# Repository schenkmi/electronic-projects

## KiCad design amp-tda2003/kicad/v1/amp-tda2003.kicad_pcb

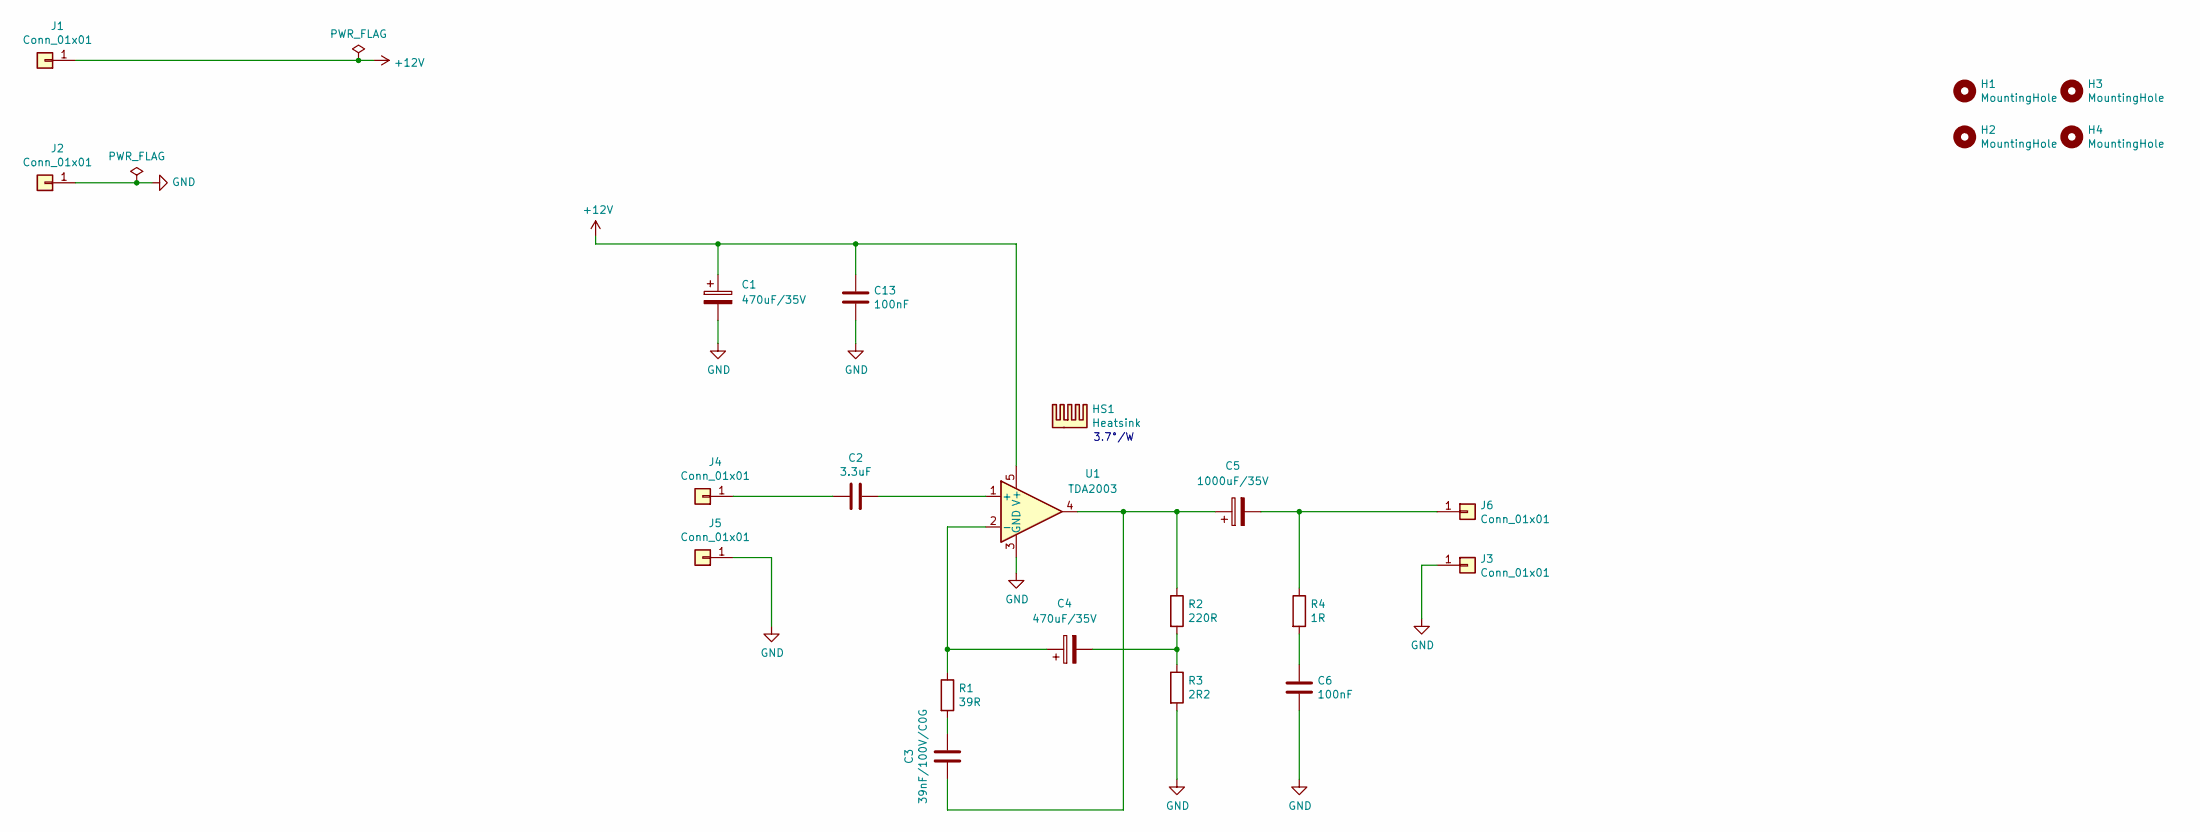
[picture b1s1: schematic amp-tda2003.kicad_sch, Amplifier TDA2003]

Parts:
C1, C4: 470uF/35V; CP_Radial_D10.0mm_P5.00mm
C2: 3.3uF; C_Rect_L7.2mm_W7.2mm_P5.00mm_FKS2_FKP2_MKS2_MKP2
C3: 39nF/100V/C0G; C_0805_2012Metric_Pad1.18x1.45mm_HandSolder
C5: 1000uF/35V; CP_Radial_D12.5mm_P5.00mm
C6, C13: 100nF; C_1206_3216Metric_Pad1.33x1.80mm_HandSolder
H1, H2, H3, H4: MountingHole; MountingHole_3.2mm_M3_Pad_Via
HS1: Heatsink; Heatsink_Fischer_SK129-STS_42x25mm_2xDrill2.5mm
J1, J2, J3, J4, J5, J6: Conn_01x01; Pin_D1.0mm_L10.0mm
R1: 39R; R_0805_2012Metric_Pad1.20x1.40mm_HandSolder
R2: 220R; R_0805_2012Metric_Pad1.20x1.40mm_HandSolder
R3: 2R2; R_0805_2012Metric_Pad1.20x1.40mm_HandSolder
R4: 1R; R_0805_2012Metric_Pad1.20x1.40mm_HandSolder
U1: TDA2003; TO-220-5_P3.4x3.7mm_StaggerOdd_Lead3.8mm_Vertical

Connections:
+12V: C1.1, C13.2, J1.1, U1.5 (V+)
GND: C1.2, C6.1, C13.1, J2.1, J3.1, J5.1, R3.2, U1.3 (GND)
unnamed: C3.1, R1.2
unnamed: C3.2, C5.1, R2.1, U1.4
unnamed: C4.2, R2.2, R3.1
unnamed: C6.2, R4.2
unnamed: C2.2, J4.1
unnamed: C5.2, J6.1, R4.1
unnamed: C2.1, U1.1 (+)
unnamed: C4.1, R1.1, U1.2 (-)

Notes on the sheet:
3.7°/W

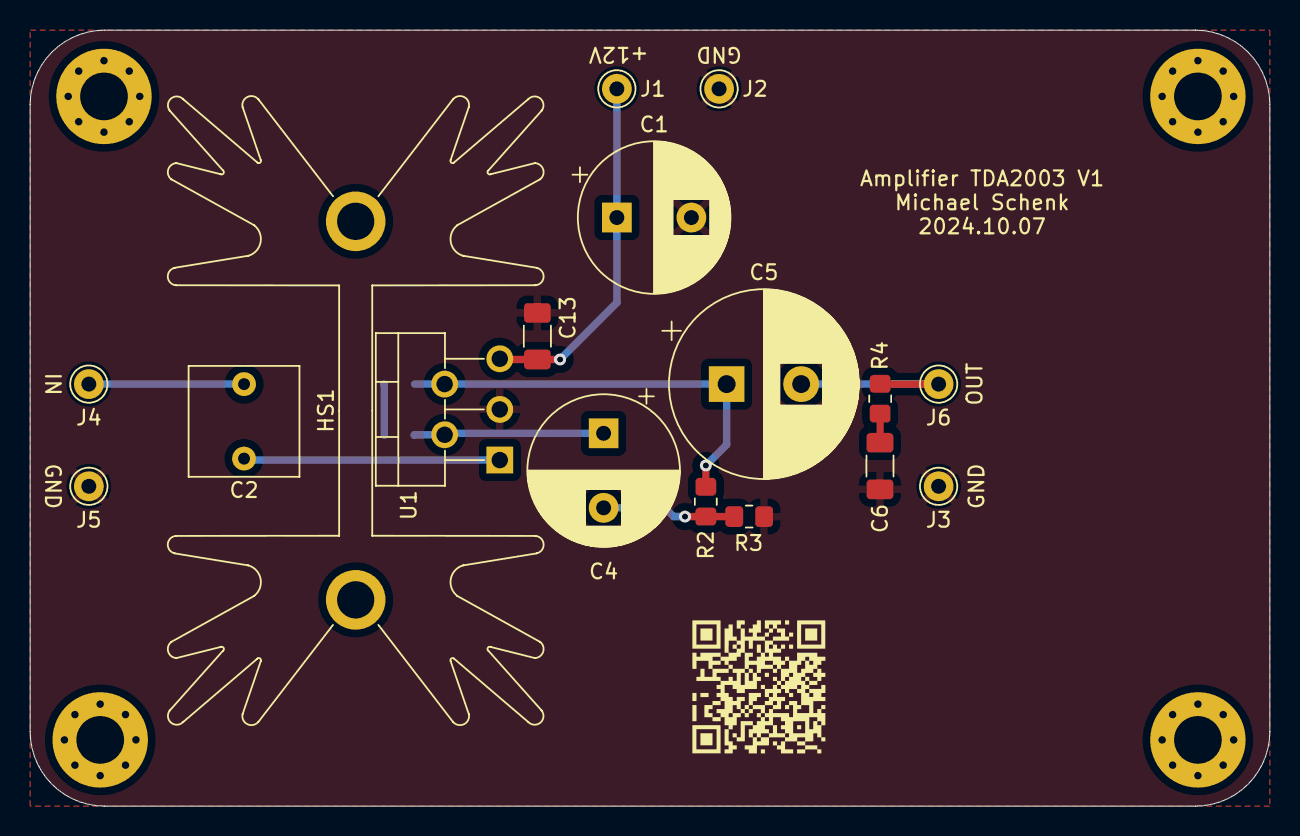
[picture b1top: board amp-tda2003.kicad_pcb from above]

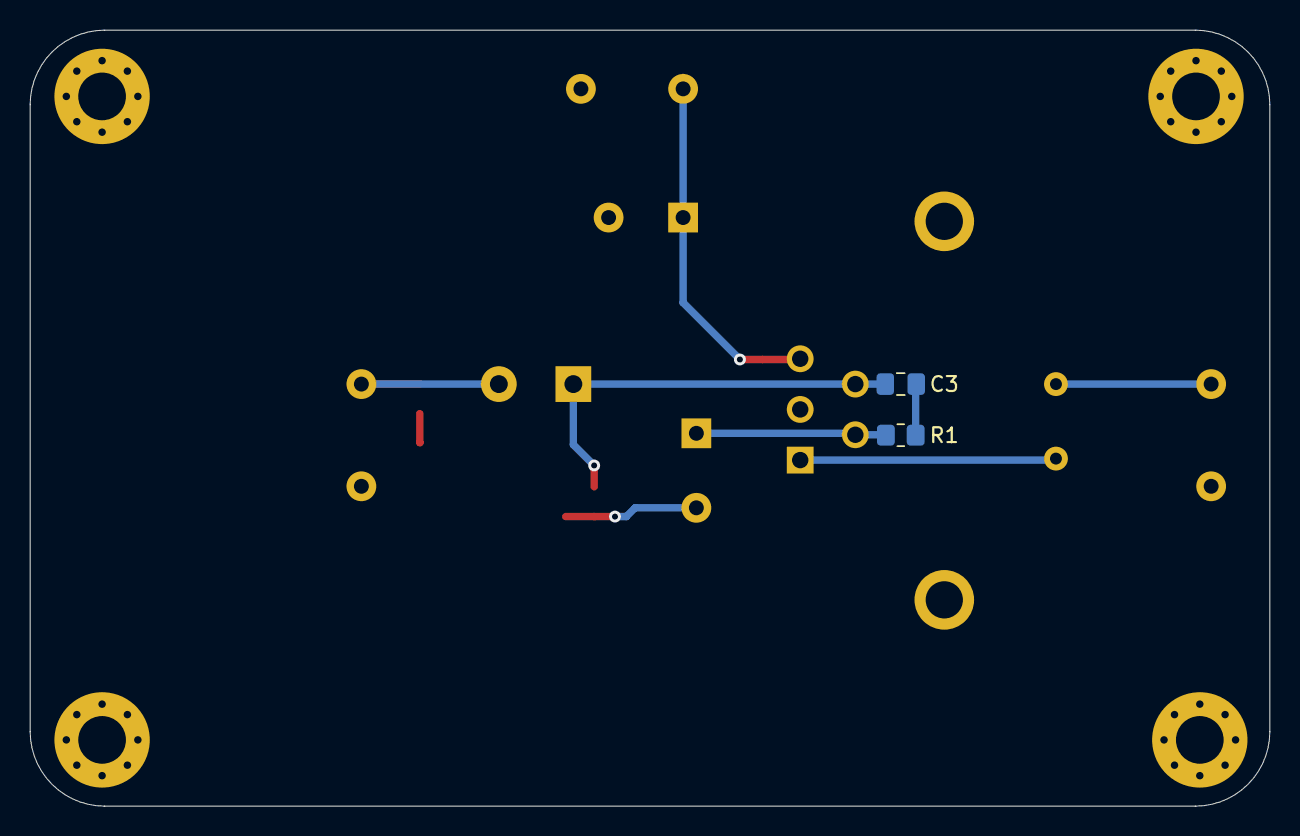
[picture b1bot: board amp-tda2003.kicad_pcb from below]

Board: 2 copper layers, 83.2 x 52.1 mm, 23 parts (2 on the bottom side), 10 nets.

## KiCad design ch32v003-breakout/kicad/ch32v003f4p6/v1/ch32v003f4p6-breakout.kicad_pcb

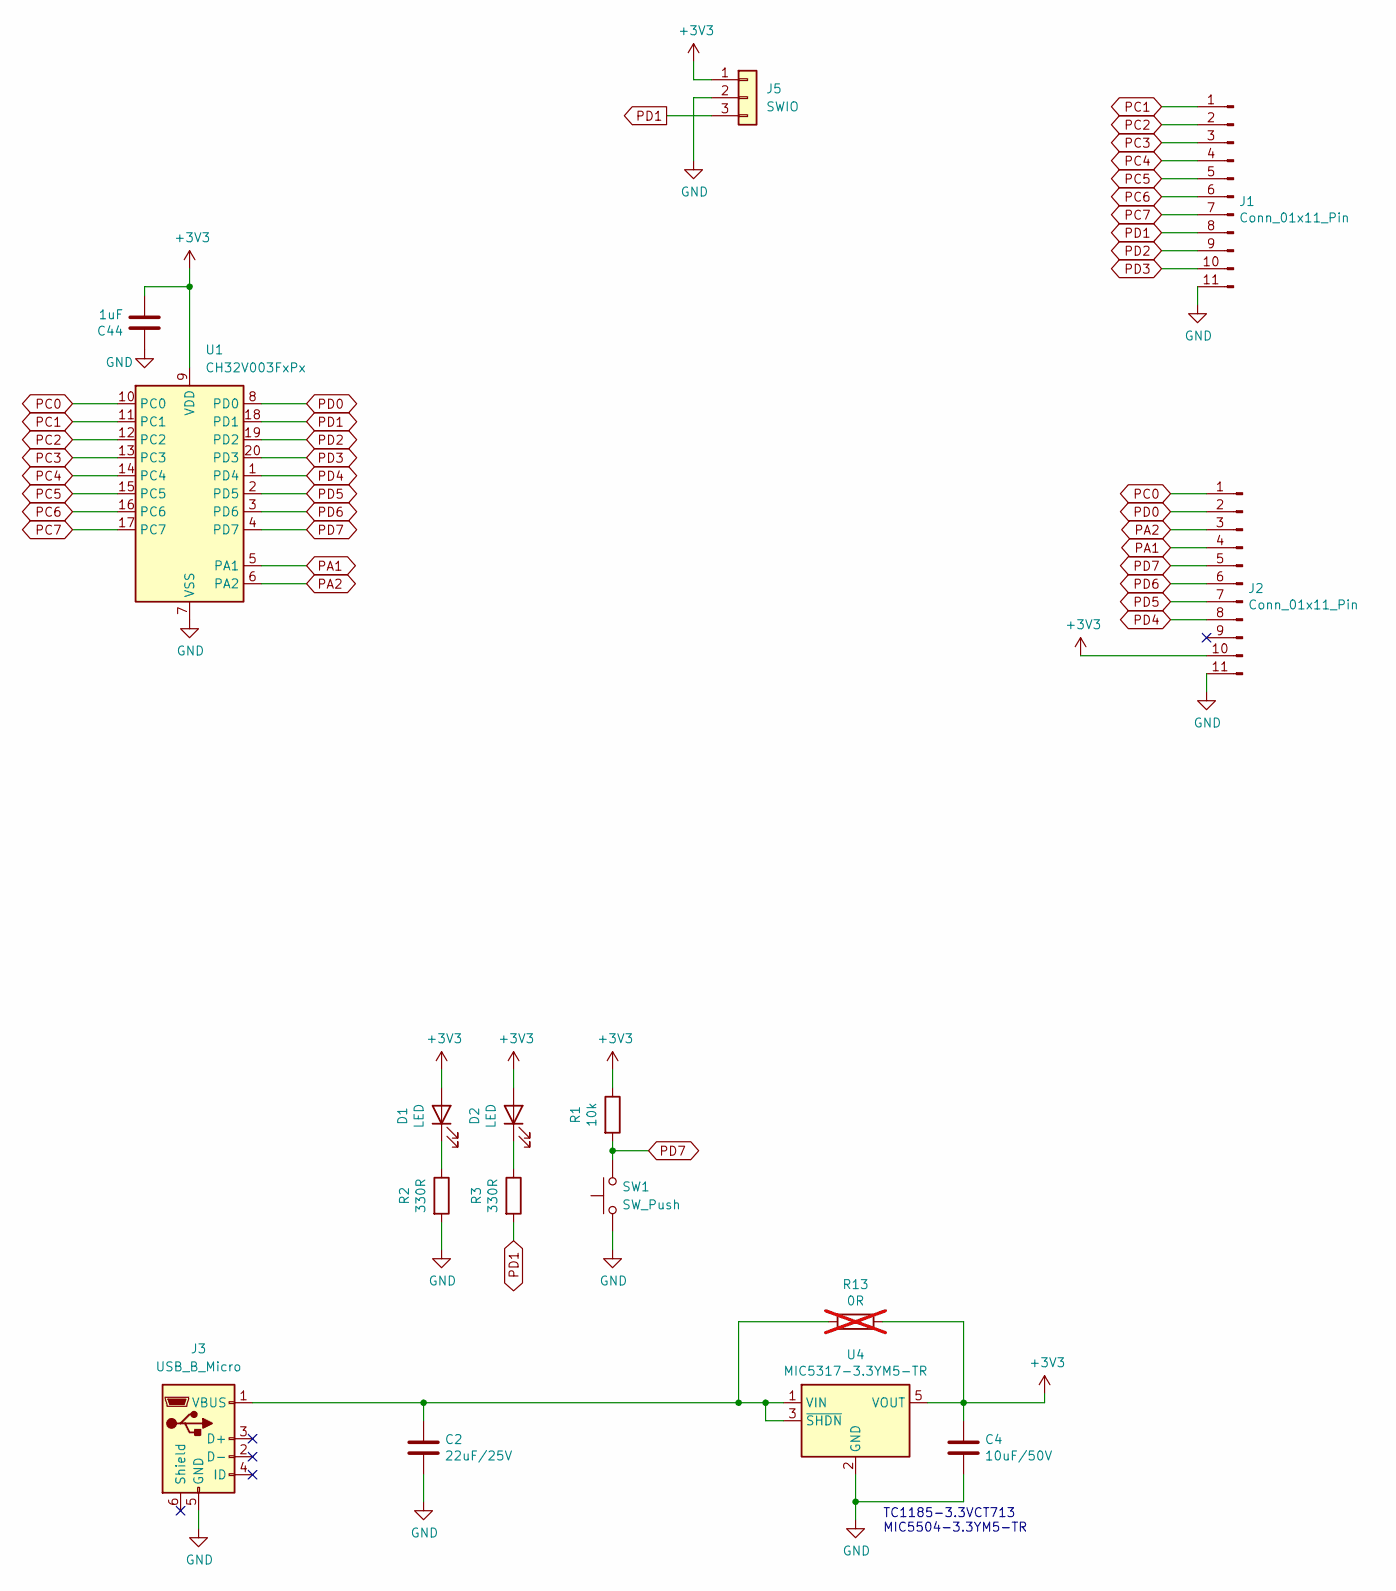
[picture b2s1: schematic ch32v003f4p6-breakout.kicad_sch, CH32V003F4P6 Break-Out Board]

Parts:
C2: 22uF/25V; C_0805_2012Metric_Pad1.18x1.45mm_HandSolder
C4: 10uF/50V; C_0805_2012Metric_Pad1.18x1.45mm_HandSolder
C44: 1uF; C_0603_1608Metric_Pad1.08x0.95mm_HandSolder
D1, D2: LED; LED_0603_1608Metric_Pad1.05x0.95mm_HandSolder
J1, J2: Conn_01x11_Pin; PinHeader_1x11_P2.54mm_Vertical
J3: USB_B_Micro; USB_Micro-B_Amphenol_10118194-0001LF_Horizontal
J5: SWIO; PinHeader_1x03_P2.54mm_Vertical
R1: 10k; R_0603_1608Metric_Pad0.98x0.95mm_HandSolder
R2, R3: 330R; R_0603_1608Metric_Pad0.98x0.95mm_HandSolder
R13: 0R; R_0603_1608Metric_Pad0.98x0.95mm_HandSolder; not fitted
SW1: SW_Push; SW_SPST_CK_RS282G05A3
U1: CH32V003FxPx; TSSOP-20_4.4x6.5mm_P0.65mm
U4: MIC5317-3.3YM5-TR; SOT-23-5

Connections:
+3V3: C4.1, C44.2, D1.2 (A), D2.2 (A), J2.10, J5.1, R1.1, R13.1, U1.9 (VDD), U4.5 (VOUT)
GND: C2.2, C4.2, C44.1, J1.11, J2.11, J3.5 (GND), J5.2, R2.2, SW1.1, U1.7 (VSS), U4.2 (GND)
unnamed: D1.1 (K), R2.1
unnamed: D2.1 (K), R3.1
unnamed: C2.1, J3.1 (VBUS), R13.2, U4.1 (VIN), U4.3 (~SHDN)
PA1: J2.4, U1.5 (PA1)
PA2: J2.3, U1.6 (PA2)
PC0: J2.1, U1.10 (PC0)
PC1: J1.1, U1.11 (PC1)
PC2: J1.2, U1.12 (PC2)
PC3: J1.3, U1.13 (PC3)
PC4: J1.4, U1.14 (PC4)
PC5: J1.5, U1.15 (PC5)
PC6: J1.6, U1.16 (PC6)
PC7: J1.7, U1.17 (PC7)
PD0: J2.2, U1.8 (PD0)
PD1: J1.8, J5.3, R3.2, U1.18 (PD1)
PD2: J1.9, U1.19 (PD2)
PD3: J1.10, U1.20 (PD3)
PD4: J2.8, U1.1 (PD4)
PD5: J2.7, U1.2 (PD5)
PD6: J2.6, U1.3 (PD6)
PD7: J2.5, R1.2, SW1.2, U1.4 (PD7)

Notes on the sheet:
TC1185-3.3VCT713 MIC5504-3.3YM5-TR

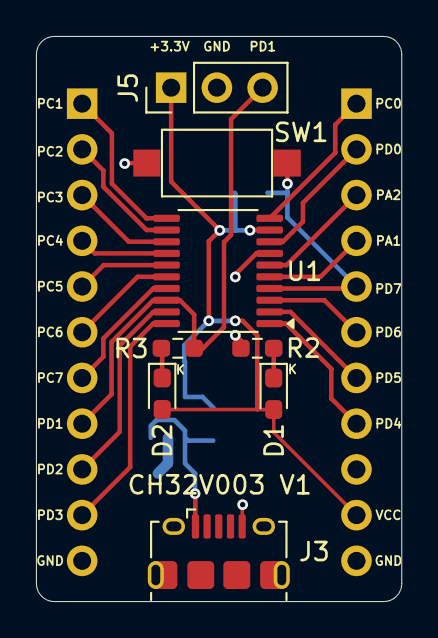
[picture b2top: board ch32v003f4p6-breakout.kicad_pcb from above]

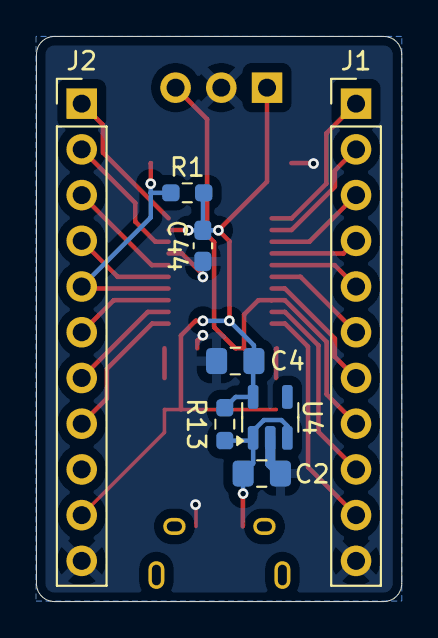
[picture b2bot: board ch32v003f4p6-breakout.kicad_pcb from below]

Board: 2 copper layers, 20.3 x 31.4 mm, 16 parts (8 on the bottom side), 23 nets.

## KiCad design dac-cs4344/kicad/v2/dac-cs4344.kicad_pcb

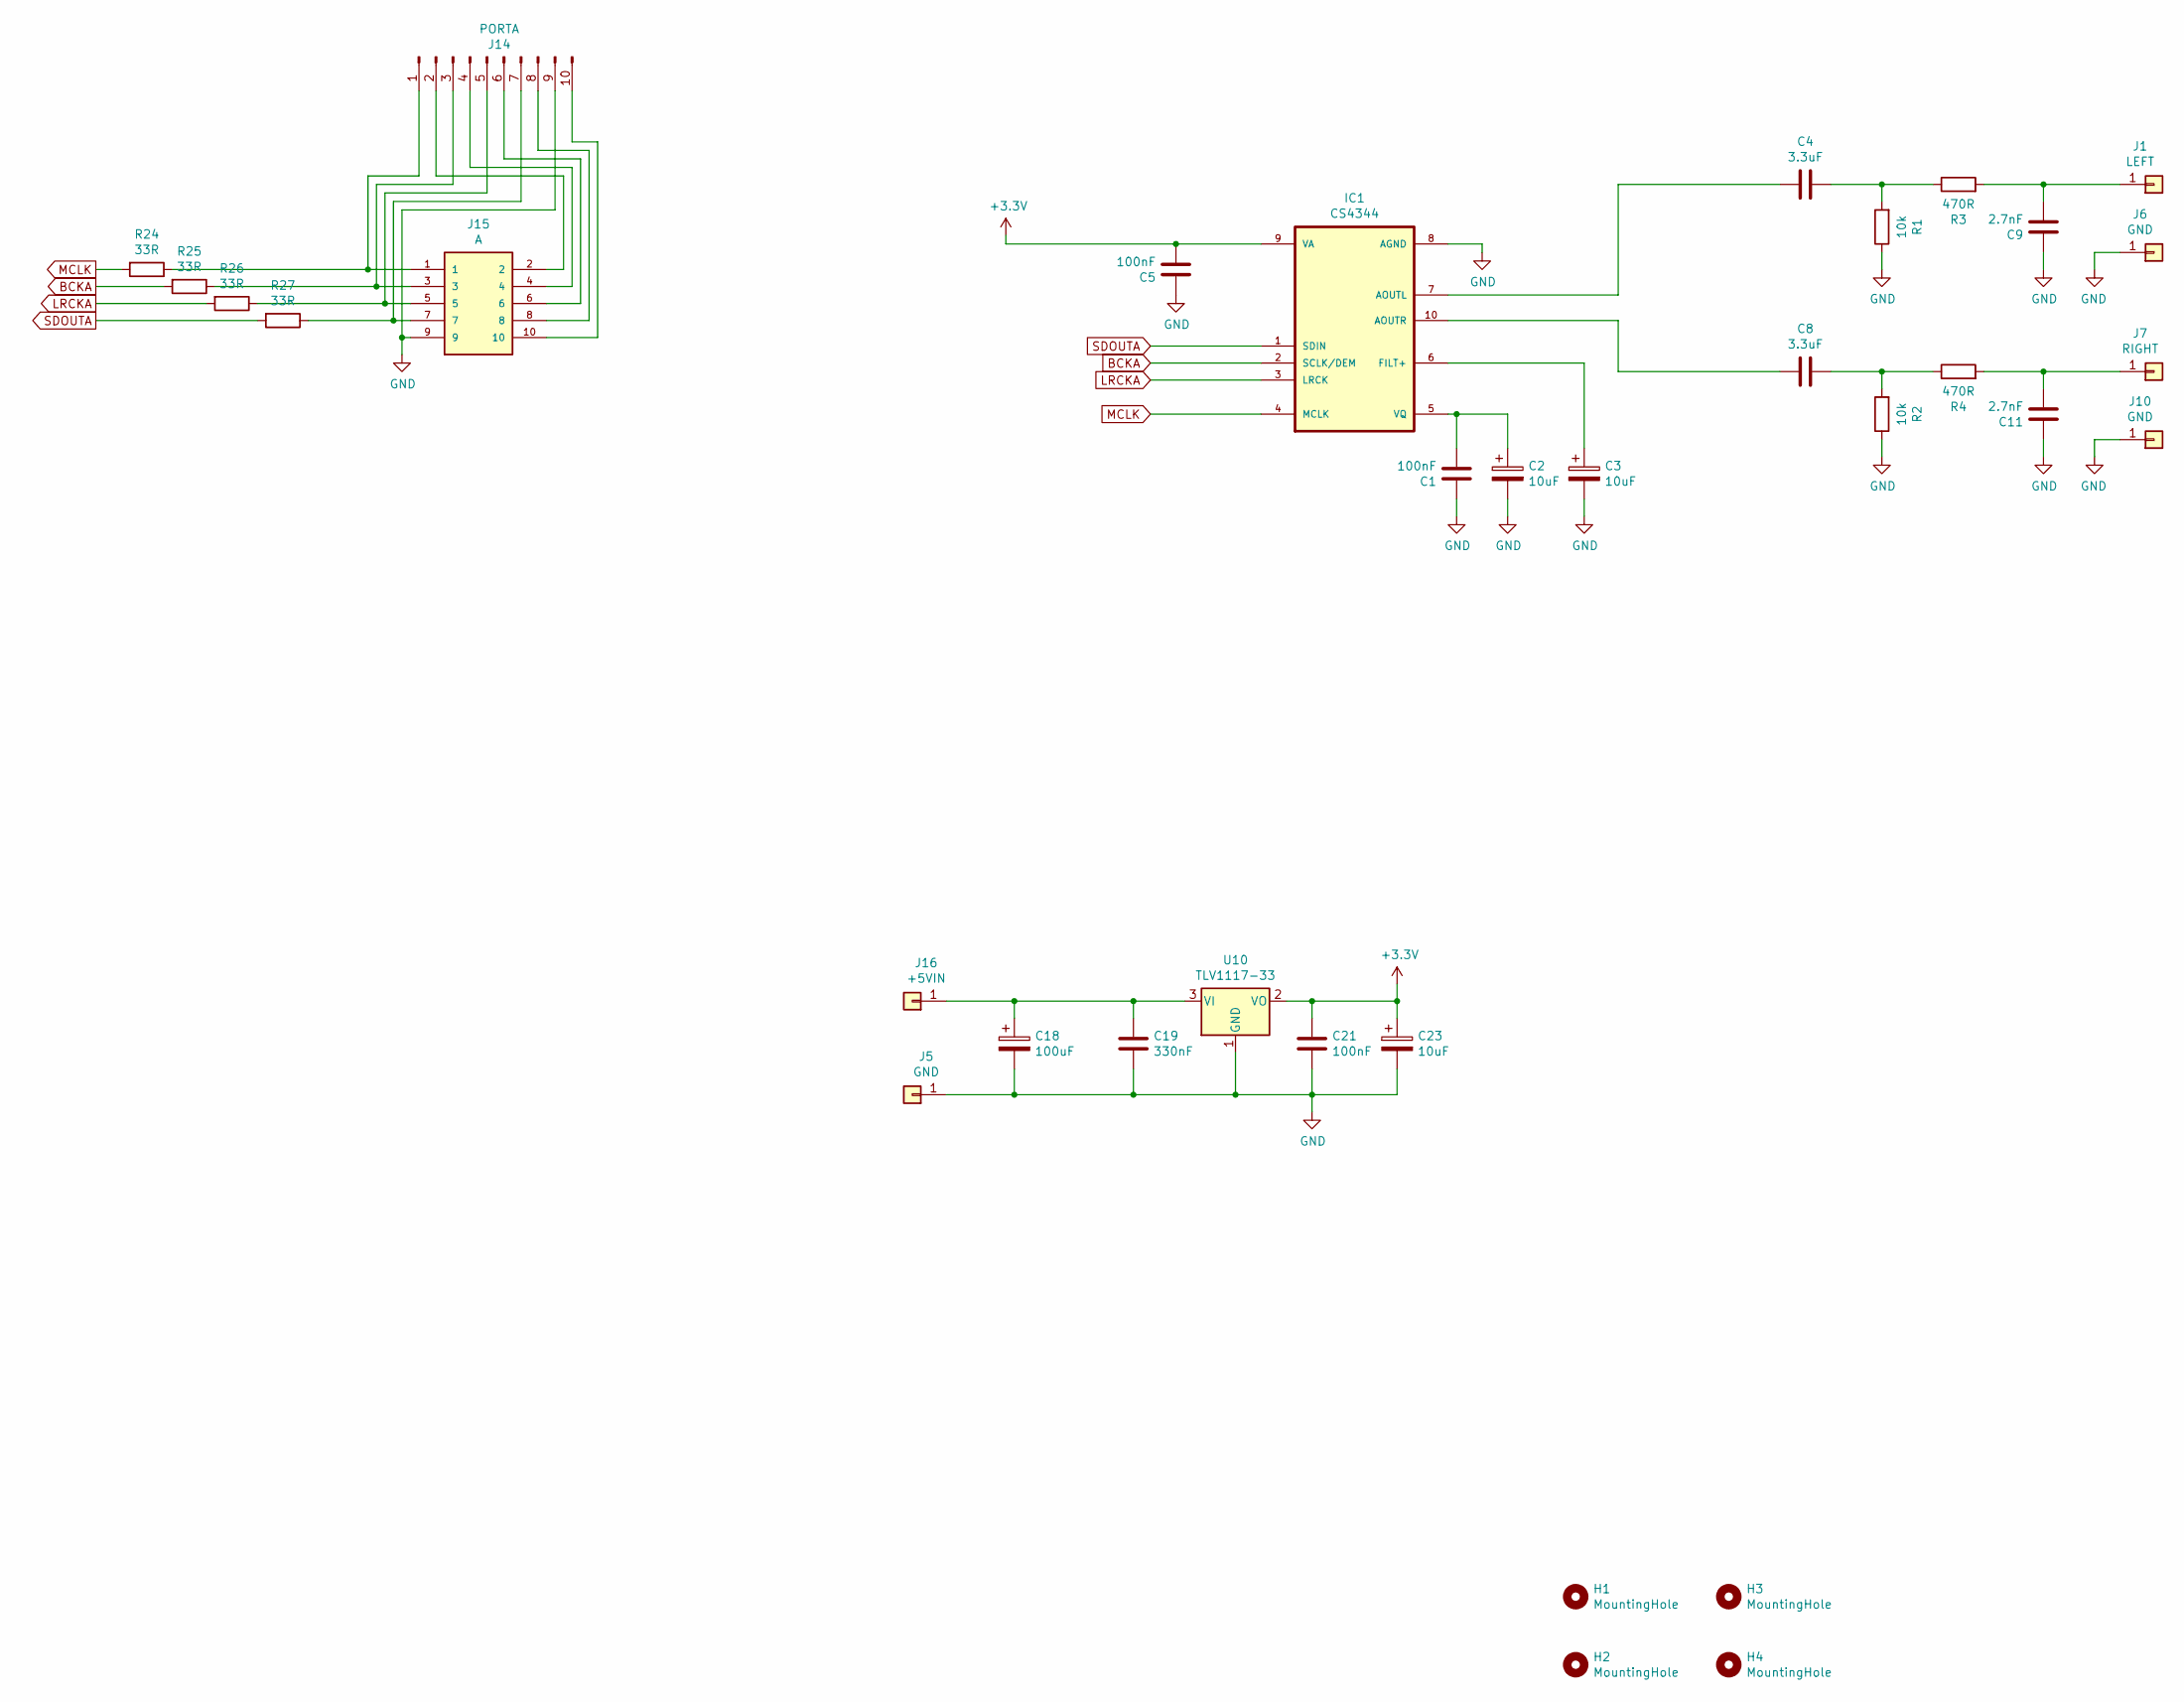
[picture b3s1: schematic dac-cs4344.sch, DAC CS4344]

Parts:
C1, C5: 100nF; C_1210_3225Metric_Pad1.33x2.70mm_HandSolder
C2, C3, C23: 10uF; CP_Radial_D6.3mm_P2.50mm
C4, C8: 3.3uF; C_1210_3225Metric_Pad1.33x2.70mm_HandSolder
C9, C11: 2.7nF; C_0805_2012Metric_Pad1.18x1.45mm_HandSolder
C18: 100uF; CP_Radial_D6.3mm_P2.50mm
C19: 330nF; C_0805_2012Metric_Pad1.18x1.45mm_HandSolder
C21: 100nF; C_0805_2012Metric_Pad1.18x1.45mm_HandSolder
H1, H2, H3, H4: MountingHole; MountingHole_3.2mm_M3
IC1: CS4344; TSSOP-10_3x3mm_P0.5mm; MPN CS4344-DZZ
J1: LEFT; Pin_D1.0mm_L10.0mm
J5, J6, J10: GND; Pin_D1.0mm_L10.0mm
J7: RIGHT; Pin_D1.0mm_L10.0mm
J14: PORTA; PinHeader_1x10_P2.54mm_Vertical
J15: A; TE_CONN_RCPT_10POS_0.1_TIN_PCB
J16: +5VIN; Pin_D1.0mm_L10.0mm
R1, R2: 10k; R_0603_1608Metric_Pad0.98x0.95mm_HandSolder
R3, R4: 470R; R_0603_1608Metric_Pad0.98x0.95mm_HandSolder
R24, R25, R26, R27: 33R; R_0603_1608Metric_Pad0.98x0.95mm_HandSolder
U10: TLV1117-33; SOT-223-3_TabPin2

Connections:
+3V3: C5.2, C21.1, C23.1, IC1.9 (VA), U10.2 (VO)
BCKA: IC1.2 (SCLK/DEM), R25.2
GND: C1.1, C2.2, C3.2, C5.1, C9.1, C11.1, C18.2, C19.2, C21.2, C23.2, IC1.8 (AGND), J5.1, J6.1, J10.1, J14.9, J15.9, R1.1, R2.1, U10.1 (GND)
LRCKA: IC1.3 (LRCK), R26.2
MCLK: IC1.4 (MCLK), R24.2
unnamed: C1.2, C2.1, IC1.5 (VQ)
unnamed: C3.1, IC1.6 (FILT+)
unnamed: C4.1, R1.2, R3.1
unnamed: C4.2, IC1.7 (AOUTL)
unnamed: C8.1, R2.2, R4.1
unnamed: C8.2, IC1.10 (AOUTR)
unnamed: C9.2, J1.1, R3.2
unnamed: C11.2, J7.1, R4.2
unnamed: C18.1, C19.1, J16.1, U10.3 (VI)
unnamed: J14.1, J15.1, R24.1
unnamed: J14.2, J15.2
unnamed: J14.3, J15.3, R25.1
unnamed: J14.4, J15.4
unnamed: J14.5, J15.5, R26.1
unnamed: J14.6, J15.6
unnamed: J14.7, J15.7, R27.1
unnamed: J14.8, J15.8
unnamed: J14.10, J15.10
SDOUTA: IC1.1 (SDIN), R27.2

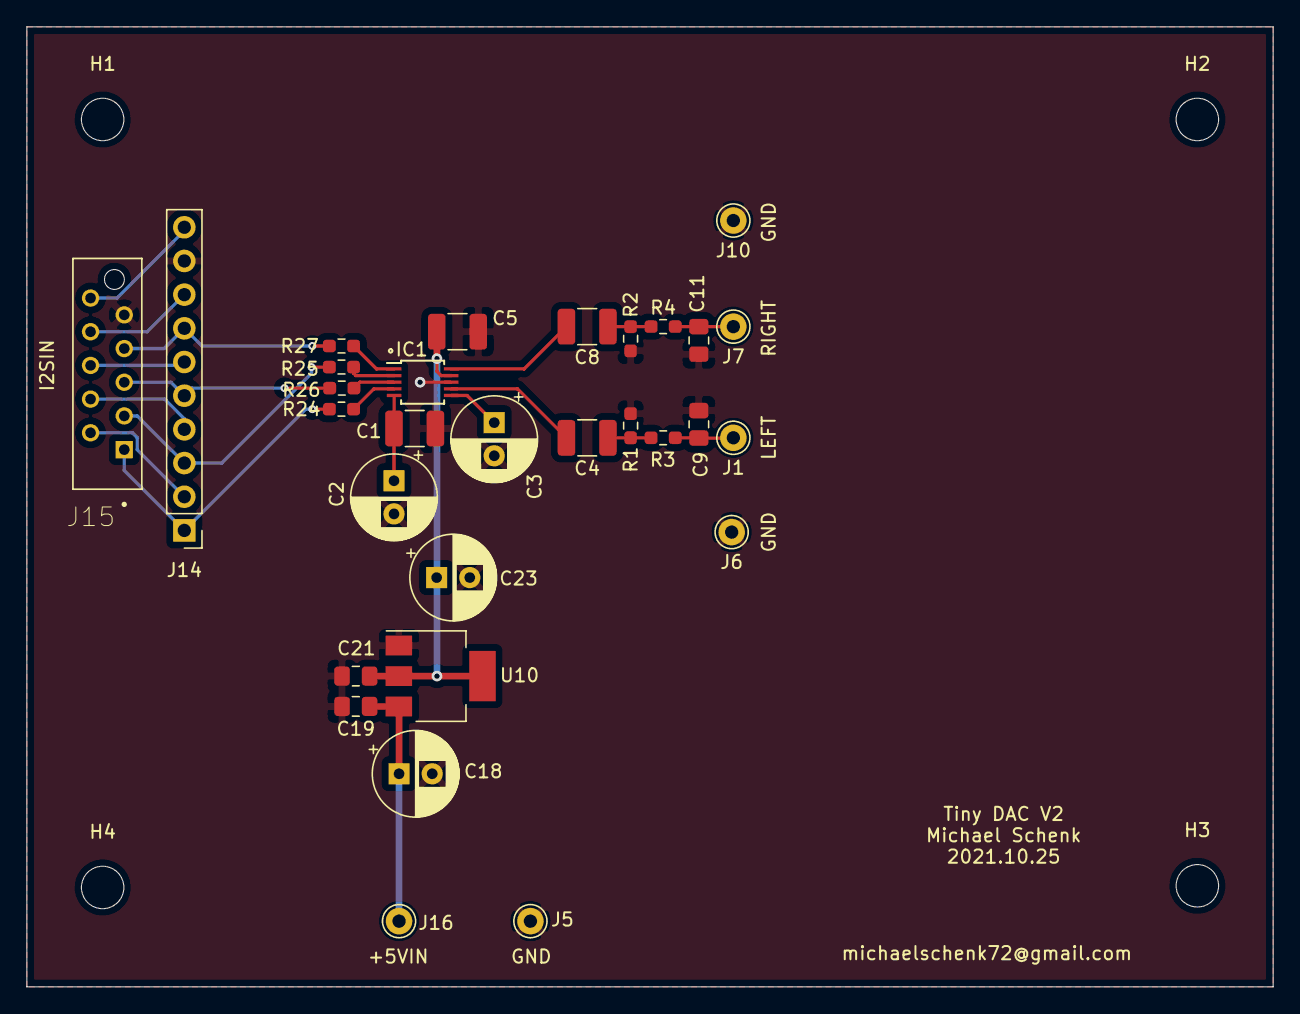
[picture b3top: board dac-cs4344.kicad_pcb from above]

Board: 2 copper layers, 94.0 x 72.4 mm, 34 parts (0 on the bottom side), 24 nets.

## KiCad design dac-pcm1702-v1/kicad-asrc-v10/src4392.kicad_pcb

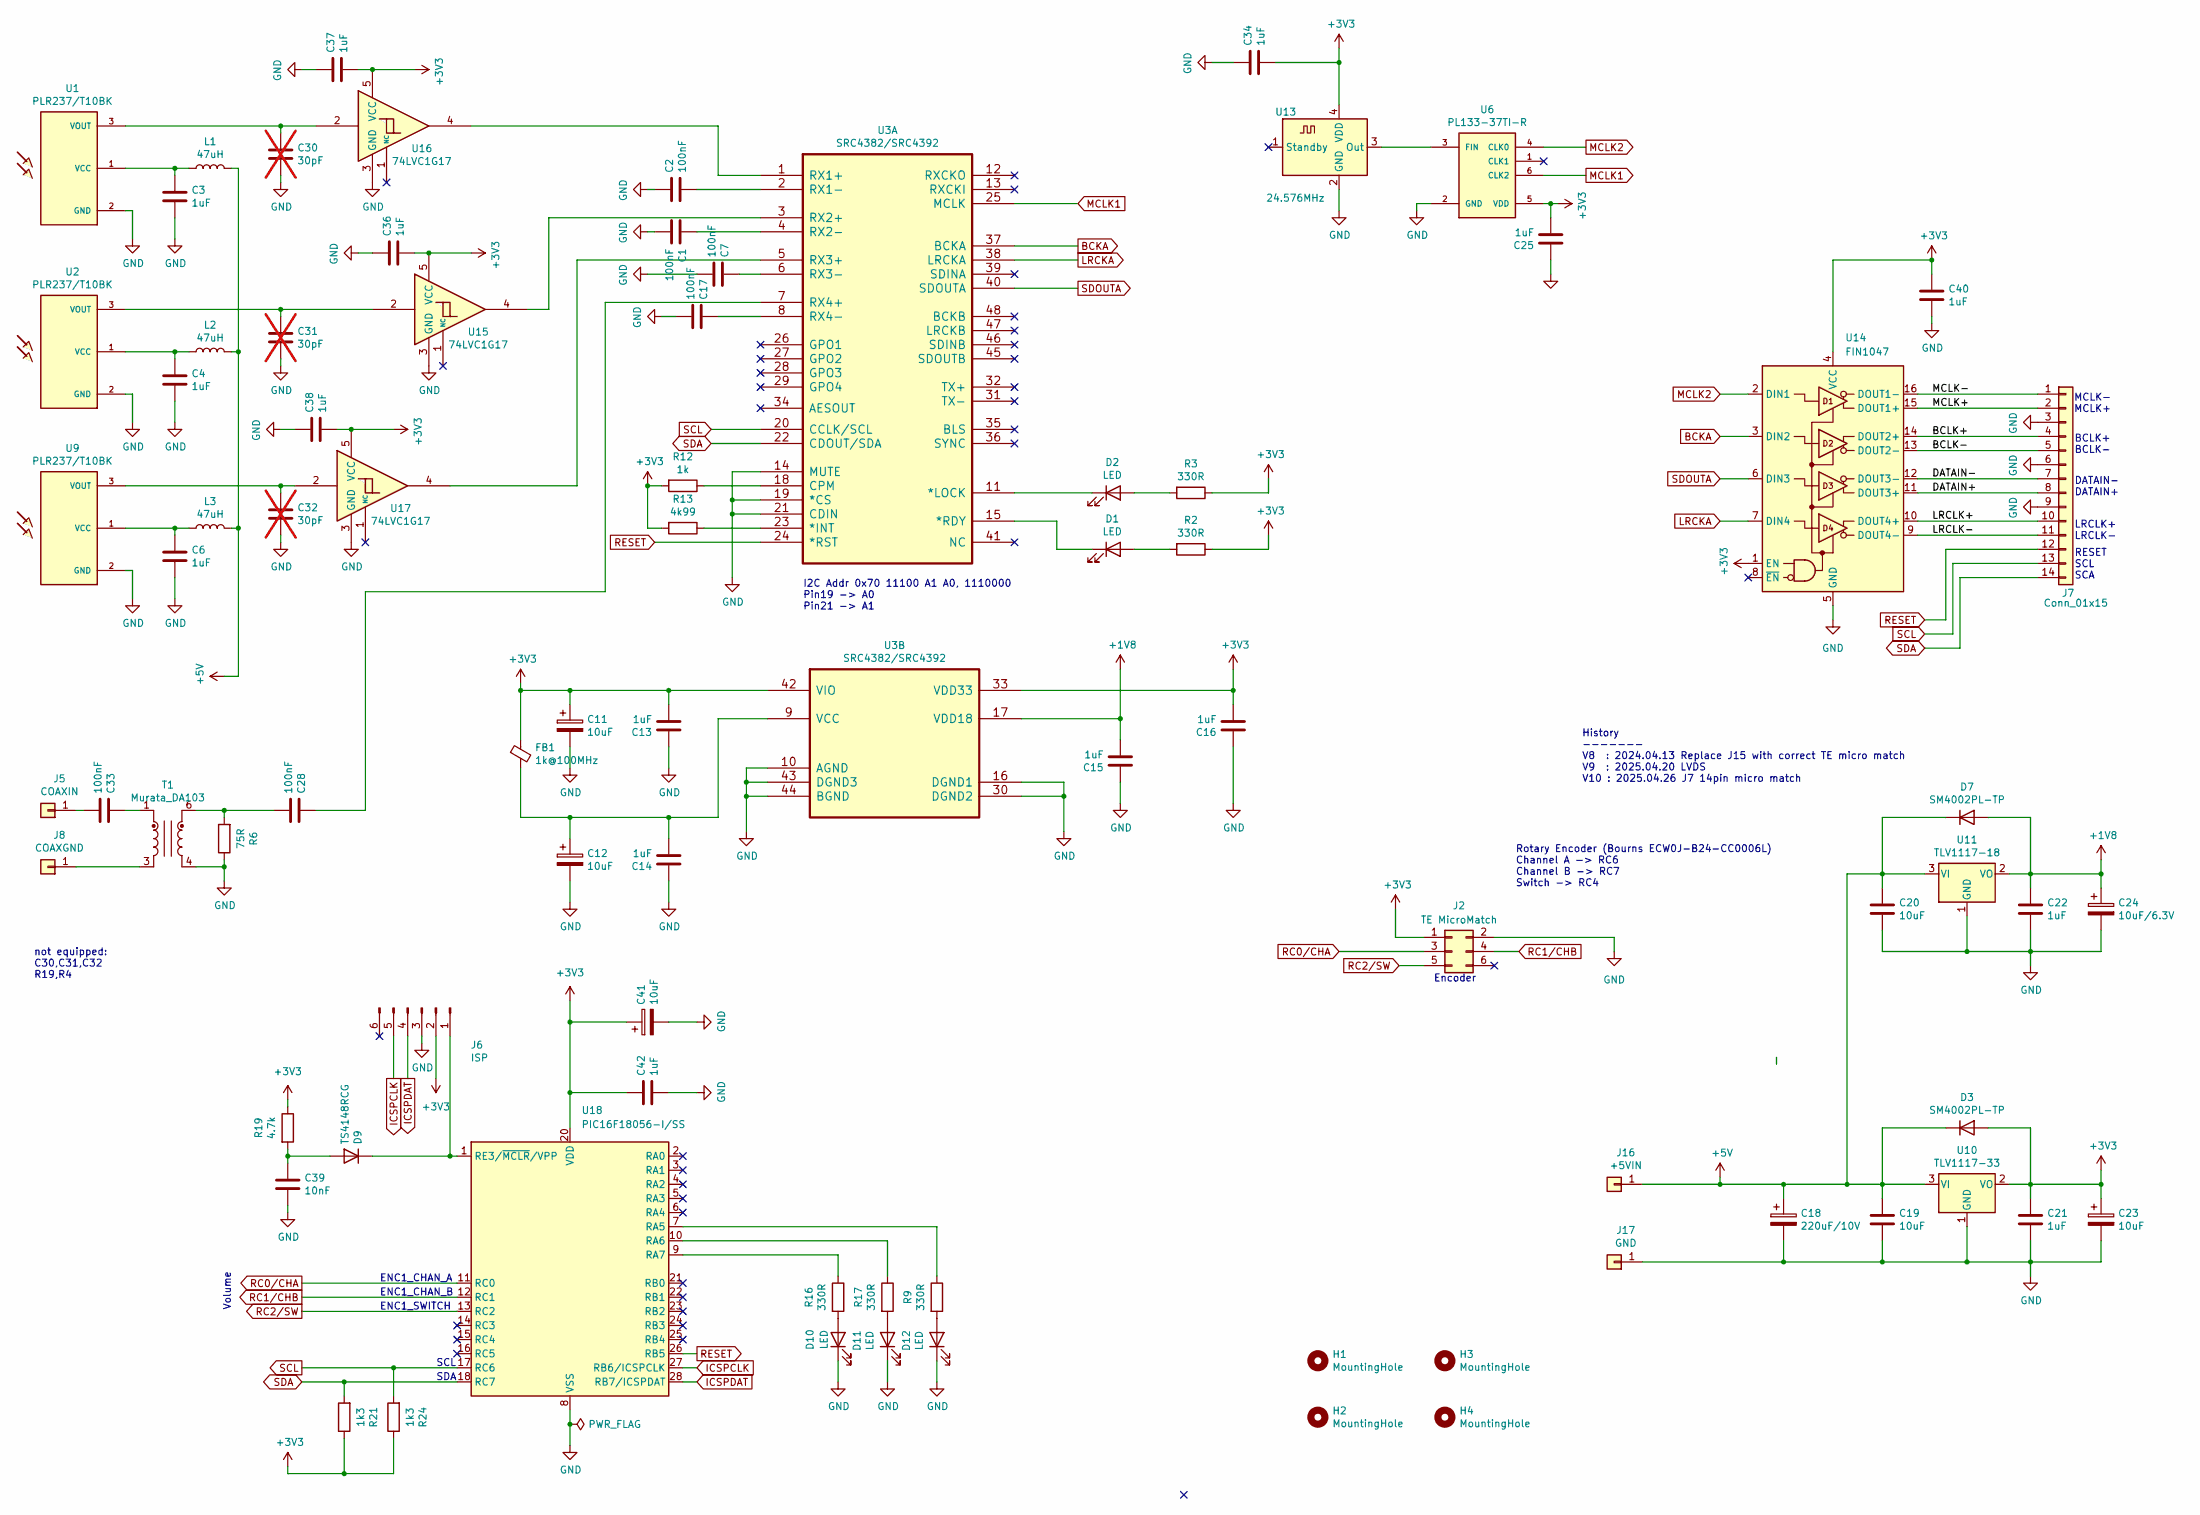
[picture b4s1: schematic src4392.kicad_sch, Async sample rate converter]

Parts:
C1, C2, C7, C17: 100nF; C_0402_1005Metric_Pad0.74x0.62mm_HandSolder
C3, C4, C6, C13, C14, C15, C16, C25, C34, C36, C37, C38, C40, C42: 1uF; C_0603_1608Metric_Pad1.08x0.95mm_HandSolder
C11, C12, C23, C41: 10uF; CP_EIA-2012-12_Kemet-R_HandSolder
C18: 220uF/10V; CP_Radial_D6.3mm_P2.50mm
C19, C20: 10uF; C_1206_3216Metric_Pad1.33x1.80mm_HandSolder
C21, C22: 1uF; C_0805_2012Metric_Pad1.18x1.45mm_HandSolder
C24: 10uF/6.3V; CP_EIA-2012-12_Kemet-R_HandSolder
C28, C33: 100nF; C_0603_1608Metric_Pad1.08x0.95mm_HandSolder
C30, C31, C32: 30pF; C_0603_1608Metric_Pad1.08x0.95mm_HandSolder; not fitted
C39: 10nF; C_0603_1608Metric_Pad1.08x0.95mm_HandSolder
D1, D2, D10, D11, D12: LED; LED_0603_1608Metric_Pad1.05x0.95mm_HandSolder
D3, D7: SM4002PL-TP; D_SOD-123F
D9: TS4148RCG; D_0603_1608Metric_Pad1.05x0.95mm_HandSolder
FB1: 1k@100MHz; C_0603_1608Metric_Pad1.08x0.95mm_HandSolder
H1, H2, H3, H4: MountingHole; MountingHole_3.2mm_M3_Pad_Via
J2: TE MicroMatch; TE_Micro-MaTch_215079-6_2x03_P1.27mm_Vertical
J5: COAXIN; Pin_D1.0mm_L10.0mm
J6: ISP; PinHeader_1x06_P2.54mm_Vertical
J7: Conn_01x15; TE_Micro-MaTch_1-215079-4_2x07_P1.27mm_Vertical
J8: COAXGND; Pin_D1.0mm_L10.0mm
J16: +5VIN; Pin_D1.0mm_L10.0mm
J17: GND; Pin_D1.0mm_L10.0mm
L1, L2, L3: 47uH; L_0805_2012Metric_Pad1.05x1.20mm_HandSolder
R2, R3, R9, R16, R17: 330R; R_0603_1608Metric_Pad0.98x0.95mm_HandSolder
R6: 75R; R_0603_1608Metric_Pad0.98x0.95mm_HandSolder
R12: 1k; R_0402_1005Metric_Pad0.72x0.64mm_HandSolder
R13: 4k99; R_0402_1005Metric_Pad0.72x0.64mm_HandSolder
R19: 4.7k; R_0603_1608Metric_Pad0.98x0.95mm_HandSolder
R21, R24: 1k3; R_0603_1608Metric_Pad0.98x0.95mm_HandSolder
T1: Murata_DA103; DA100J
U1, U2, U9: PLR237/T10BK; PLR135-T10_PLT133-T10W
U3: SRC4382/SRC4392; TQFP-48_7x7mm_P0.5mm
U6: PL133-37TI-R; SOT-23-6
U10: TLV1117-33; SOT-223-3_TabPin2
U11: TLV1117-18; SOT-223-3_TabPin2
U13: 24.576MHz; Oscillator_SMD_EuroQuartz_XO32-4Pin_3.2x2.5mm_HandSoldering
U14: FIN1047; TSSOP-16_4.4x5mm_P0.65mm; Part Number FIN1047MTCX
U15, U16, U17: 74LVC1G17; SOT-23-5
U18: PIC16F18056-I/SS; SSOP-28_5.3x10.2mm_P0.65mm

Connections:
+1V8: C15.2, C22.1, C24.1, D7.2 (A), U3.17 (VDD18), U11.2 (VO)
+3V3: C11.1, C13.2, C16.2, C21.1, C23.1, C25.2, C34.1, C36.1, C37.1, C38.1, C40.1, C41.1, C42.1, D3.2 (A), FB1.1, J2.1, J6.2, R2.1, R3.1, R12.2, R13.2, R19.1, R21.1, R24.1, U3.33 (VDD33), U3.42 (VIO), U6.5 (VDD), U10.2 (VO), U13.4 (VDD), U14.1 (EN), U14.4 (VCC), U15.5 (VCC), U16.5 (VCC), U17.5 (VCC), U18.20 (VDD)
+5V: C18.1, C19.1, C20.1, D3.1 (K), D7.1 (K), J16.1, L1.2, L2.2, L3.2, U10.3 (VI), U11.3 (VI)
/BCLK+: J7.4, U14.14 (DOUT2+)
/BCLK-: J7.5, U14.13 (DOUT2-)
/DATAIN+: J7.8, U14.11 (DOUT3+)
/DATAIN-: J7.7, U14.12 (DOUT3-)
/LRCLK+: J7.10, U14.10 (DOUT4+)
/LRCLK-: J7.11, U14.9 (DOUT4-)
/MCLK+: J7.2, U14.15 (DOUT1+)
/MCLK-: J7.1, U14.16 (DOUT1-)
BCKA: U3.37 (BCKA), U14.3 (DIN2)
GND: C1.1, C2.2, C3.1, C4.1, C6.1, C7.1, C11.2, C12.2, C13.1, C14.1, C15.1, C16.1, C17.1, C18.2, C19.2, C20.2, C21.2, C22.2, C23.2, C24.2, C25.1, C30.1, C31.1, C32.1, C34.2, C36.2, C37.2, C38.2, C39.2, C40.2, C41.2, C42.2, D10.1 (K), D11.1 (K), D12.1 (K), J2.2, J6.3, J7.3, J7.6, J7.9, J17.1, R6.1, T1.4, U1.2 (GND), U2.2 (GND), U3.10 (AGND), U3.14 (MUTE), U3.16 (DGND1), U3.19 (*CS), U3.21 (CDIN), U3.30 (DGND2), U3.43 (DGND3), U3.44 (BGND), U6.2 (GND), U9.2 (GND), U10.1 (GND), U11.1 (GND), U13.2 (GND), U14.5 (GND), U15.3 (GND), U16.3 (GND), U17.3 (GND), U18.8 (VSS), U18.19 (VSS)
ICSPCLK: J6.5, U18.27 (RB6/ICSPCLK)
ICSPDAT: J6.4, U18.28 (RB7/ICSPDAT)
LRCKA: U3.38 (LRCKA), U14.7 (DIN4)
MCLK1: U3.25 (MCLK), U6.6 (CLK2)
MCLK2: U6.4 (CLK0), U14.2 (DIN1)
unnamed: C28.1, R6.2, T1.6
unnamed: C33.2, T1.1
unnamed: D1.2 (A), R2.2
unnamed: D1.1 (K), U3.15 (*RDY)
unnamed: D2.2 (A), R3.2
unnamed: D2.1 (K), U3.11 (*LOCK)
unnamed: C39.1, D9.2 (A), R19.2
unnamed: D9.1 (K), J6.1, U18.1 (RE3/~MCLR/VPP)
unnamed: D10.2 (A), R16.2
unnamed: D11.2 (A), R17.2
unnamed: D12.2 (A), R9.2
unnamed: C33.1, J5.1
unnamed: J8.1, T1.3
unnamed: C3.2, L1.1, U1.1 (VCC)
unnamed: C30.2, U1.3 (VOUT), U16.2
unnamed: C4.2, L2.1, U2.1 (VCC)
unnamed: C31.2, U2.3 (VOUT), U15.2
unnamed: R13.1, U3.23 (*INT)
unnamed: R12.1, U3.18 (CPM)
unnamed: U3.1 (RX1+), U16.4
unnamed: C2.1, U3.2 (RX1-)
unnamed: U3.3 (RX2+), U15.4
unnamed: C1.2, U3.4 (RX2-)
unnamed: U3.5 (RX3+), U17.4
unnamed: C7.2, U3.6 (RX3-)
unnamed: C28.2, U3.7 (RX4+)
unnamed: C17.2, U3.8 (RX4-)
unnamed: C12.1, C14.2, FB1.2, U3.9 (VCC)
unnamed: C6.2, L3.1, U9.1 (VCC)
unnamed: C32.2, U9.3 (VOUT), U17.2
unnamed: U6.3 (FIN), U13.3 (Out)
unnamed: R9.1, U18.7 (RA5)
unnamed: R17.1, U18.10 (RA6)
unnamed: R16.1, U18.9 (RA7)
RC0/CHA: J2.3, U18.11 (RC0)
RC1/CHB: J2.4, U18.12 (RC1)
RC2/SW: J2.5, U18.13 (RC2)
RESET: J7.12, U3.24 (*RST), U18.26 (RB5)
SCL: J7.13, R24.2, U3.20 (CCLK/SCL), U18.17 (RC6)
SDA: J7.14, R21.2, U3.22 (CDOUT/SDA), U18.18 (RC7)
SDOUTA: U3.40 (SDOUTA), U14.6 (DIN3)

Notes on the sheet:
ENC1_CHAN_B
I2C Addr 0x70 11100 A1 A0, 1110000 Pin19 -> A0 Pin21 -> A1
History ------- V8 : 2024.04.13 Replace J15 with correct TE micro match V9 : 2025.04.20 LVDS V10 : 2025.04.26 J7 14pin micro match
ENC1_CHAN_A
SDA
DATAIN- DATAIN+
LRCLK+ LRCLK-
MCLK- MCLK+
ENC1_SWITCH
Rotary Encoder (Bourns ECW0J-B24-CC0006L) Channel A -> RC6 Channel B -> RC7 Switch -> RC4
Volume
BCLK+ BCLK-
Encoder
not equipped: C30,C31,C32 R19,R4
SCL
RESET SCL SCA
